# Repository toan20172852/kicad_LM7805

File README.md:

# **Sumary**
- Voltage Regulator with Output 5V/1A Using LM7805 for Smoothing.
- This Project on way learn Kicad
# **Reference**
- Information IC LM7805: https://pdf1.alldatasheet.com/datasheet-pdf/view/82833/FAIRCHILD/LM7805.html
- Guilde using Kicad: https://www.youtube.com/watch?v=uYEVXo8IzLs&list=PLLb0wIuhHnH22__SY4lo0tVAaMEDcjebu&index=201~
- Kicad forum in VietNam: https://www.facebook.com/groups/314655419877107
# Image of project
- Schematic of LM7805

- PCB layout of Project

- Image 3D of project

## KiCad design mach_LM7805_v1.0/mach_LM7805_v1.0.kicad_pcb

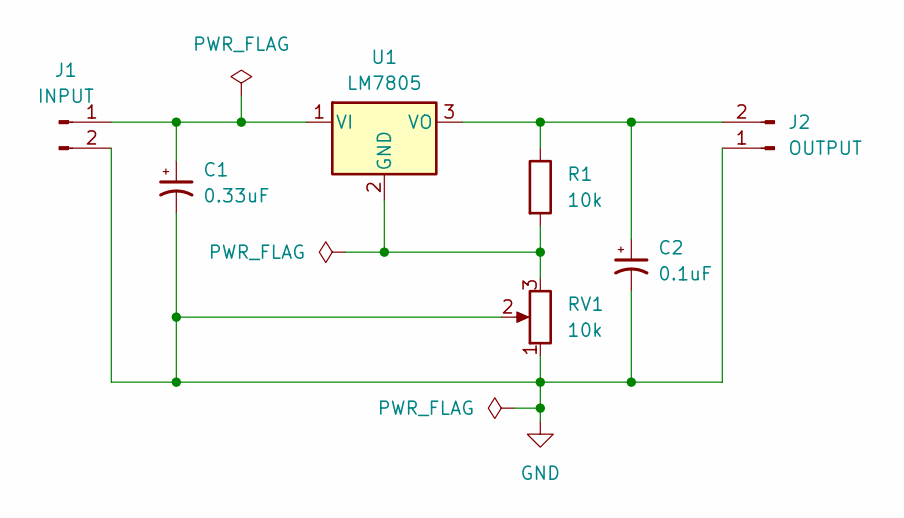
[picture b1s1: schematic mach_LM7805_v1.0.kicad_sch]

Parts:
C1: 0.33uF; CP_Radial_D5.0mm_P2.00mm
C2: 0.1uF; CP_Radial_D5.0mm_P2.00mm
J1: INPUT; PinHeader_1x02_P2.54mm_Vertical
J2: OUTPUT; PinHeader_1x02_P2.54mm_Vertical
R1: 10k; R_Axial_DIN0207_L6.3mm_D2.5mm_P10.16mm_Horizontal
RV1: 10k; Potentiometer_Piher_T-16H_Single_Horizontal
U1: LM7805; TO-220-3_Horizontal_TabDown

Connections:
GND: C1.2, C2.2, J1.2, J2.1, RV1.1, RV1.2
unnamed: C1.1, J1.1, U1.1 (VI)
unnamed: C2.1, J2.2, R1.1, U1.3 (VO)
unnamed: R1.2, RV1.3, U1.2 (GND)

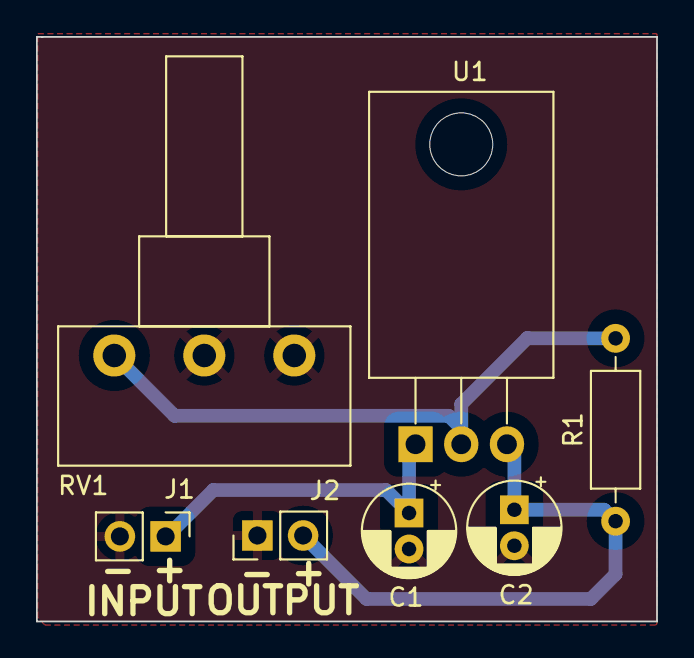
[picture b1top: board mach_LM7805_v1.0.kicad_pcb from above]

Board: 2 copper layers, 34.5 x 32.5 mm, 7 parts (0 on the bottom side), 4 nets.

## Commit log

2023-09-07 Final Project
2023-09-07 modify readme.md and update image
2023-09-07 modify readme.md
